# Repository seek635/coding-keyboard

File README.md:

# ClaudePad

专为 Claude Code 打造的 ZMK 宏键盘：11 个按键，把权限切换、打断、模型切换、`@` 文件引用和语音对讲映射到实体键上。

- 固件：ZMK（Seeed XIAO nRF52840，ZMK 板名 `xiao_ble//zmk`）
- 上位机：Windows + Python 3.12，零第三方依赖
- PCB：2 层、90 × 76 mm、1.6 mm；XIAO 为 **14 个穿孔焊盘（2×7 2.54mm 排针）**，11 个二极管、14 颗 Choc V2 轴
- 外壳：3D 打印底座 + 定位板 + 键帽，整机约 108 × 82 × 23.1 mm；控制器仓敞开，USB-C/RESET 可直接操作；后壁 USB-C 开口已按排针高度上移
- 主控：XIAO 自带 USB-C、**可按的 RESET 键**、锂电池充电与 BAT 焊盘；通过 **2×7 2.54mm 排针穿孔焊接**
- 供电：**无电源开关**，JST 电池插头 + ZMK 深度睡眠；长期存放时拔掉电池

更多预览：[正俯视](docs/preview/claudepad-top.png)｜[爆炸图](docs/preview/claudepad-exploded.png)｜[PCB](docs/preview/claudepad-pcb.png)｜**焊接 3D 指导图**：[正面](docs/3d/guide-front-iso.png) / [俯视布局](docs/3d/guide-top.png) / [背面](docs/3d/guide-bottom-iso.png) / [总装](docs/3d/guide-assembled.png)

## 键位

```
PERM   MODEL   CMD    ↑    VOICE
STOP   (空)           ←    ↓    →
ENTER (2u)          SPACE (3u)
```

| 键 | 单击 | 双击 | 长按 |
|---|---|---|---|
| PERM | `Shift+Tab` 循环权限档位（另发 `F16` 供上位机同步档位） | — | 250ms → `Ctrl+Alt+Shift+F15`（上位机复位到 default） |
| MODEL | 输入 `/model` + Enter | — | 250ms → `Ctrl+Alt+Shift+F14`（上位机循环模型） |
| CMD | `/` | — | 200ms → `@` |
| STOP | `Esc` 打断 | 200ms 内双击 → `Ctrl+C` | 1200ms → `Ctrl+C` ×2 退出会话 |
| ENTER | `Enter` | 200ms 内双击 → `Shift+Enter` | — |
| SPACE | `Space` | — | 300ms → `Tab`（带三重防误触） |
| VOICE | `Space` | 180ms 内双击 → `/voice` | 按住 → `Space` 对讲 |
| ← ↑ ↓ → | 方向键，系统原生自动重复 | — | — |

> 审批功能已取消：没有拨杆、没有自动批准。Claude Code 的权限提示仍由人工回答。PERM 单击额外发送一个 **F16** 同步信号，让上位机在 Claude Code 不暴露当前档位的情况下仍能准确计算复位次数。

## 仓库结构

```
build.yaml / .github/workflows/build.yml   ZMK 构建
config/west.yml                            ZMK manifest
config/boards/shields/claudepad/           shield：矩阵、布局、键位
pcb/                                       KiCad PCB、封装、Gerber、BOM、设计包
cad/                                       OpenSCAD 外壳/定位板/键帽 + STL
host/                                      Windows 上位机
  claudepad_host/                          守护进程、动作、安装器、状态逻辑
  scripts/                                 statusLine / hooks 脚本
  tests/                                   单元测试
docs/BOM.md                                购物清单
docs/pcb.md                                PCB 制造、网络表、焊接顺序
docs/cad.md                                外壳/定位板/键帽打印与装配
docs/wiring.md                             手工飞线备用方案
docs/keymap.md                             键位与时间参数
docs/preview/                              成品/PCB 预览图
tools/check_firmware.py                    固件静态检查
tools/check_cad.py                         STL 尺寸与闭合检查
tools/check_hardware.py                    PCB ↔ 外壳坐标一致性检查
```

## 0. 制造硬件

1. **PCB**：把 `pcb/output/claudepad-jlcpcb-gerbers.zip` 发给嘉立创/JLCPCB，选 **2 层、1.6mm、1oz、无铅喷锡**，不需要 SMT 贴片。完整设计（KiCad 工程 + 制造文件 + BOM + 3D）在 `pcb/output/claudepad-pcb-design.zip`。DRC 已通过：0 错误、0 未连接。
2. **外壳**：先打印 `cad/output/stl/test_coupon.stl`，用真实轴体确定 `SWITCH_PLATE_GAP`，修改 `cad/params.scad` 后重新导出；再打印底座、定位板、键帽。详见 [docs/cad.md](docs/cad.md)。
3. **焊接**：按 [docs/pcb.md](docs/pcb.md) 的顺序先焊 XIAO 电池线，再把 XIAO 焊到 2×7 2.54mm 排针、插入 PCB 的 14 个穿孔，然后焊轴体、二极管、JST。排针焊完后从背面把过长针脚剪到 ≤4mm。注意 XIAO 的 BAT 焊盘在背面，要先处理电池线再装模块。
4. **装配**：PCB 放在底座支撑柱上 → 装定位板 → 4 颗 M2×6 自攻螺丝 → 键帽 → 接电池。

## 1. 编译固件

把整个目录推到 GitHub 仓库即可：`.github/workflows/build.yml` 会调用 ZMK 官方 workflow，在 Actions 里产出 `claudepad-xiao_ble__zmk-zmk.uf2`（以 Actions 产物名为准）。

```bash
git init
git add .
git commit -m "ClaudePad v1"
git branch -M main
git remote add origin https://github.com/<用户名>/<仓库名>.git
git push -u origin main
```

推上去就自动触发构建；绿勾后在该次 run 页面底部 **Artifacts** 下载 `firmware`，里面是 `claudepad-xiao_ble__zmk-zmk.uf2`。仓库需是空仓库（不要先勾 README/.gitignore）；后续改键位再 `git commit && git push` 会重新构建。

本地编译需要 west + Zephyr SDK，参考 [ZMK 本地构建文档](https://zmk.dev/docs/development/local-toolchain/build)。

刷机：**双击 XIAO 板上 USB-C 旁边的 RESET 键**进入 bootloader，把 `.uf2` 拖进去。首次使用在系统蓝牙里配对 `ClaudePad`。

> XIAO 的 USB-C 与 RESET 键在同一条边；外壳后壁有 USB-C 凹槽/开口，控制器仓敞开，刷机时可直接按 RESET。电池通过 XIAO 背面 BAT 焊盘 → PCB 窗口 → BAT1/JST 连接（详见 docs/pcb.md）。

## 2. 安装上位机（Windows）

需要 Python 3.10+（已在 3.12 上测试），不需要安装任何第三方包。

```bash
cd host
python -m claudepad_host install
python -m claudepad_host run
```

- `install` 会备份 `~/.claude/settings.json`，然后把 hooks 和 statusLine 指向 `~/.claude/claudepad/` 下的脚本。
- `run` 启动守护进程，监听复位 `F15`、模型 `F14`、档位同步 `F16`。
- 开机自启：`python -m claudepad_host install --autostart`。
- 查看状态：`python -m claudepad_host status`。
- 卸载：`python -m claudepad_host uninstall`（会恢复安装前的 statusLine）。

也可以双击 `host/install.bat`、`host/run.bat`。

### 上位机做了什么

- **PERM 长按**：读取当前权限档位，按官方循环 `default → acceptEdits → plan → auto → default` 计算需要按几次 `Shift+Tab`，然后注入。
- **MODEL 长按**：读取 statusLine 里的当前模型，发送 `/model <下一个>` + Enter。
- **statusLine**：持续把模型名、cwd 写进状态目录，并在终端显示 `ClaudePad | 模型 | 目录 | 上下文%`。
- **不再自动批准**：`PermissionRequest` hook 只写入权限档位，不返回 allow/deny。

### 配置

`%LOCALAPPDATA%\ClaudePad\config.json`：

```json
{
  "models": ["opus", "sonnet", "haiku"],
  "permission_cycle": ["default", "acceptEdits", "plan", "auto"],
  "assume_mode": "auto"
}
```

- 如果你的会话里启用了 `bypassPermissions`，把它按实际顺序加入 `permission_cycle`。
- 修改后重启守护进程生效。

## 3. 验证

```bash
python -m unittest discover -s host/tests -v
python tools/check_firmware.py
python tools/check_hardware.py
python tools/check_cad.py
```

- `check_firmware.py` 校验 11 个矩阵交点、11 个键位顺序、引脚、信号绑定。
- `check_hardware.py` 校验 PCB 与外壳的键位、键帽、XIAO 和板框坐标一致。
- `check_cad.py` 校验 6 个 STL 的尺寸与网格闭合（0 条非流形边）。
- PCB：KiCad DRC **0 violations / 0 unconnected**，报告在 `pcb/output/drc.rpt`；Gerber、BOM 和设计包在 `pcb/output/`。
- XIAO 通过 2×7 2.54mm 排针抬高约 2.5mm；外壳控制器仓敞开，后壁 USB-C 开口已上移到 z≈10.5–14.3。RESET 仍可直接按。
- 电池线从 XIAO 背面 BAT 焊盘直接引到 JST 旁的 BAT1；主板下方没有电池窗口或额外穿孔（只有 14 个排针孔）。
- 二极管在轴位之间的空行里水平焊接，不在任何轴位正下方；背面短丝印线标阴极。
- `R1/C1` 是设计空位（STOP 右侧、MODEL 正下方），不装轴；不要按 3×5 把这一格补满。
- 固件最终是否能编译，以 GitHub Actions 为准（本机未安装 Zephyr SDK）。
- 上位机的真实按键行为需要接上硬件后在 Claude Code 终端里手动验证。

## 已知限制

- 注入按键发送到**当前前台窗口**；触发复位/模型循环时请保持 Claude Code 终端聚焦。
- 多会话时上位机选择“最近更新的会话”。
- 手动 `Shift+Tab` 改档位后，权限状态可能短暂过期；`PermissionRequest` / `UserPromptSubmit` / `Stop` hooks 会尽快刷新。
- `/model <alias>` 会同时把该模型保存为**新会话默认模型**（Claude Code 官方行为）。
- 没有物理电源开关：靠 ZMK 深度睡眠省电，长期存放请拔掉 JST 电池插头。
- 2u / 3u 的 Choc V2 键帽比 1u 难买；买不到时可用 `cad/output/stl/keycap_2u.stl` / `keycap_3u.stl` 打印。
- 轴板间隙 `SWITCH_PLATE_GAP` 必须用 `test_coupon.stl` 实测校准；不同批次的 Choc V2 可能差 0.5–1mm。
- 外壳控制器仓是敞开的；如果介意落灰，可自行加一块简单防尘片，不要遮住 USB-C/RESET。
- 3D 预览中的 PCB 没有加载元件 3D 模型；成品外观以 CAD 预览为准。

## 文档

- [购物清单](docs/BOM.md)
- [PCB 制造与焊接](docs/pcb.md)
- [外壳/定位板/键帽](docs/cad.md)
- [手工飞线备用方案](docs/wiring.md)
- [键位与时间参数](docs/keymap.md)
- [上位机说明与排错](host/README.md)
- [设计规格](docs/superpowers/specs/2026-10-23-claudepad-design.md)
- [实施计划](docs/superpowers/plans/2026-10-23-claudepad.md)

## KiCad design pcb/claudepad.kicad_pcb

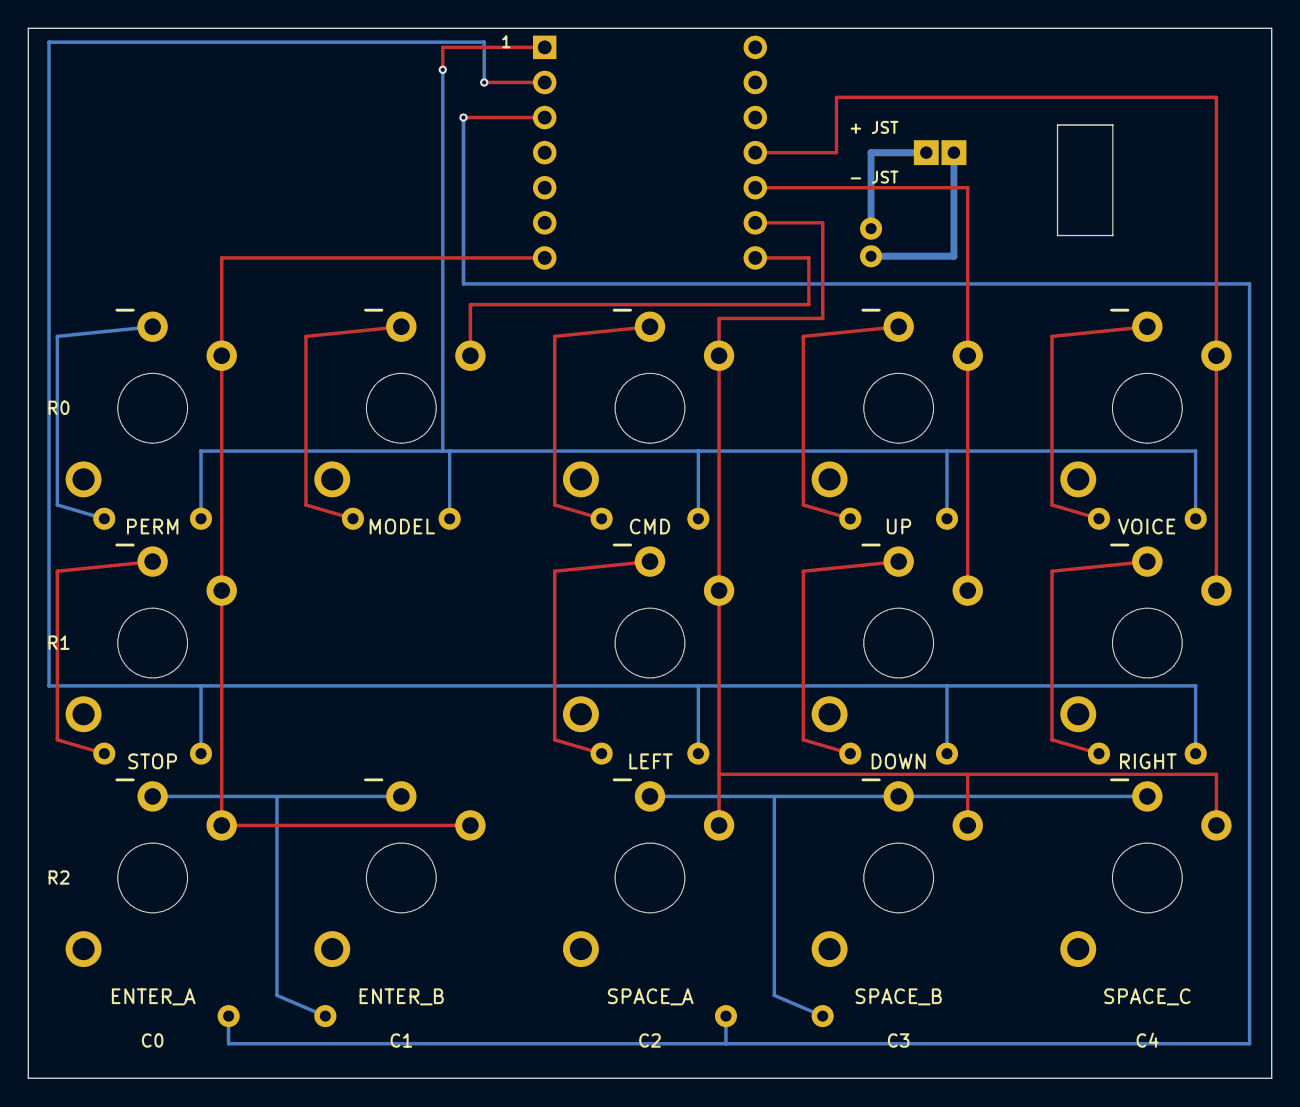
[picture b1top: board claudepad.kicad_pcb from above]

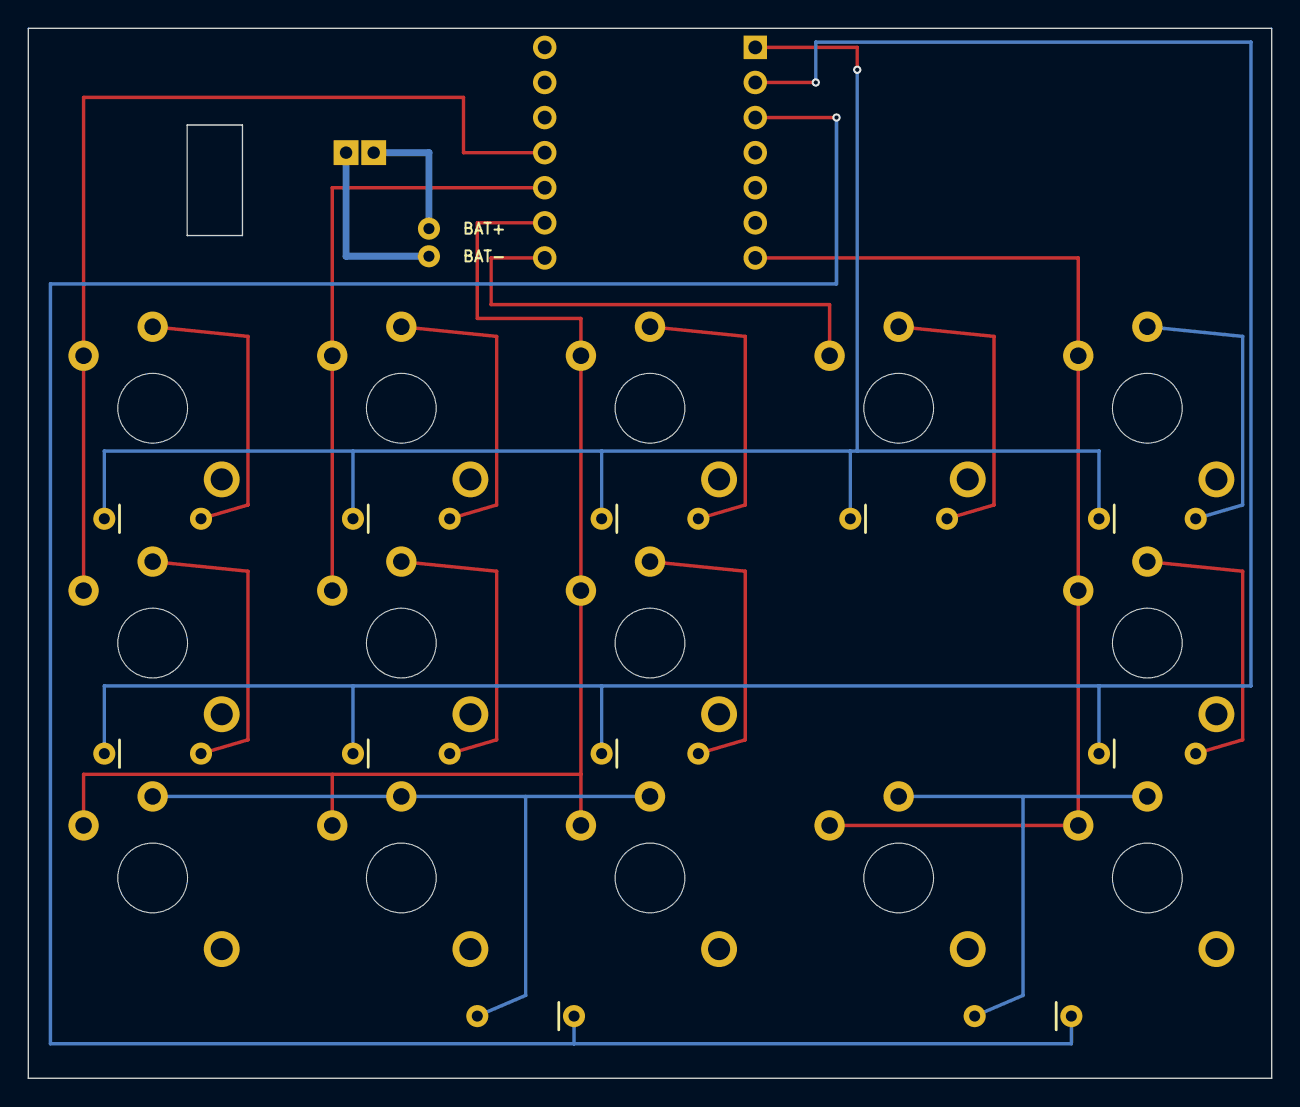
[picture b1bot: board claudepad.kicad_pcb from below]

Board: 2 copper layers, 90.0 x 76.0 mm, 28 parts (12 on the bottom side), 21 nets.

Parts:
BAT1: PCB solder pads; BAT_WIRE_PADS
D1, D2, D3, D4, D5, D6, D7, D8, D9, D10, D11: 1N4148 DO-35; D_1N4148_DO35
J1: JST-PH 2.0 2P; JST_PH_2.00mm_THT
SW1, SW2, SW3, SW4, SW5, SW6, SW7, SW8, SW9, SW10, SW11, SW12, SW13, SW14: Kailh Choc V2 1u; SW_Kailh_Choc_V2_1.00u
U1: Seeed XIAO nRF52840 (THT headers); XIAO-nRF52840-THT-ClaudePad

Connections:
ANODE_CMD: D3.1, SW3.1
ANODE_DOWN: D8.1, SW8.1
ANODE_ENTER: D10.1, SW10.1, SW11.1
ANODE_LEFT: D7.1, SW7.1
ANODE_MODEL: D2.1, SW2.1
ANODE_PERM: D1.1, SW1.1
ANODE_RIGHT: D9.1, SW9.1
ANODE_SPACE: D11.1, SW12.1, SW13.1, SW14.1
ANODE_STOP: D6.1, SW6.1
ANODE_UP: D4.1, SW4.1
ANODE_VOICE: D5.1, SW5.1
BAT+: BAT1.1, J1.1
BAT-: BAT1.2, J1.2
COL0: SW1.2, SW6.2, SW10.2, SW11.2, U1.7
COL1: SW2.2, U1.8
COL2: SW3.2, SW7.2, SW12.2, SW13.2, SW14.2, U1.9
COL3: SW4.2, SW8.2, U1.10
COL4: SW5.2, SW9.2, U1.11
ROW0: D1.2, D2.2, D3.2, D4.2, D5.2, U1.1
ROW1: D6.2, D7.2, D8.2, D9.2, U1.2
ROW2: D10.2, D11.2, U1.3

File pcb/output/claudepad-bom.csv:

References,Value,Footprint,Quantity
D1 D2 D3 D4 D5 D6 D7 D8 D9 D10 D11,1N4148 DO-35,D_1N4148_DO35,11
J1,JST-PH 2.0 2P,JST_PH_2.00mm_THT,1
SW1 SW2 SW3 SW4 SW5 SW6 SW7 SW8 SW9 SW10 SW11 SW12 SW13 SW14,Kailh Choc V2 1u,SW_Kailh_Choc_V2_1.00u,14
U1,Seeed XIAO nRF52840 (THT headers),XIAO-nRF52840-THT-ClaudePad,1

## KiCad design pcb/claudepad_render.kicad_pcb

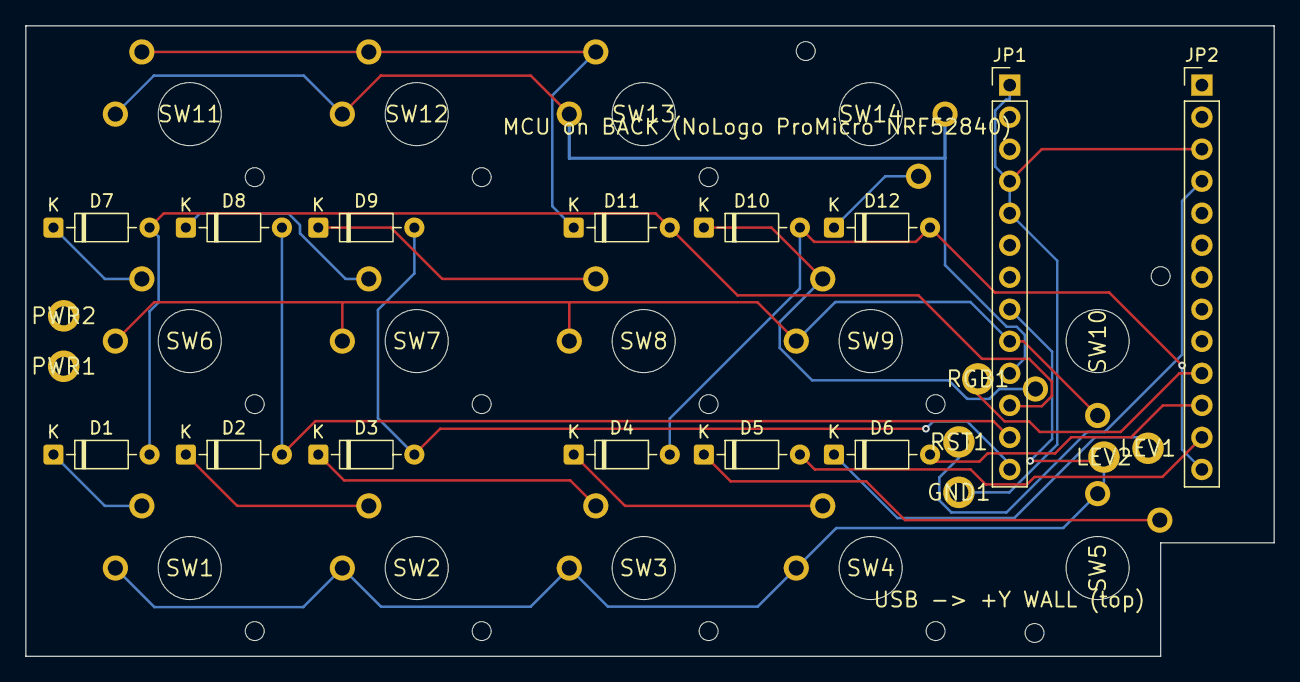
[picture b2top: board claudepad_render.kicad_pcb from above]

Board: 2 copper layers, 99.0 x 50.0 mm, 35 parts (0 on the bottom side), 24 nets.

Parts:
D1, D2, D3, D4, D5, D6, D7, D8, D9, D10, D11, D12: 1N4148; D_DO-35_SOD27_P7.62mm_Horizontal
GND1: 复位按钮
JP1, JP2: MCU; PinHeader_1x13_P2.54mm_Vertical
LEV1: 拨杆 NO
LEV2: 拨杆 COM
PWR1, PWR2: 电源开关(飞线)
RGB1: D15 预留
RST1: 复位按钮
SW1, SW2, SW3, SW4, SW5, SW6, SW7, SW8, SW9, SW10, SW11, SW12, SW13, SW14: ChocV2

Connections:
APPROVE_MID: D6.1, LEV1.1
COL1: D1.2, D7.2, D11.2, JP1.11
COL2: D2.2, D8.2, JP1.12
COL3: D3.2, D9.2, JP1.13
COL4: D4.2, D10.2, D12.2, JP2.13
COL5: D5.2, JP2.12
COL6: D6.2, JP2.11
GND: GND1.1, JP1.1, JP1.4, JP1.5, JP2.3
MID_R1C1: D1.1, SW1.1
MID_R1C2: D2.1, SW2.1
MID_R1C3: D3.1, SW3.1
MID_R1C4: D4.1, SW4.1
MID_R1C5: D5.1, SW5.1
MID_R2C1: D7.1, SW6.1
MID_R2C2: D8.1, SW7.1
MID_R2C3: D9.1, SW8.1
MID_R2C4: D10.1, SW9.1, SW10.1
MID_R3C1: D11.1, SW11.1, SW12.1, SW13.1
MID_R3C4: D12.1, SW14.1
RGB_DIN: JP2.10, RGB1.1
ROW1: JP1.8, LEV2.1, SW1.2, SW2.2, SW3.2, SW4.2, SW5.2
ROW2: JP1.9, SW6.2, SW7.2, SW8.2, SW9.2, SW10.2
ROW3: JP1.10, SW11.2, SW12.2, SW13.2, SW14.2
RST: JP2.4, RST1.1
